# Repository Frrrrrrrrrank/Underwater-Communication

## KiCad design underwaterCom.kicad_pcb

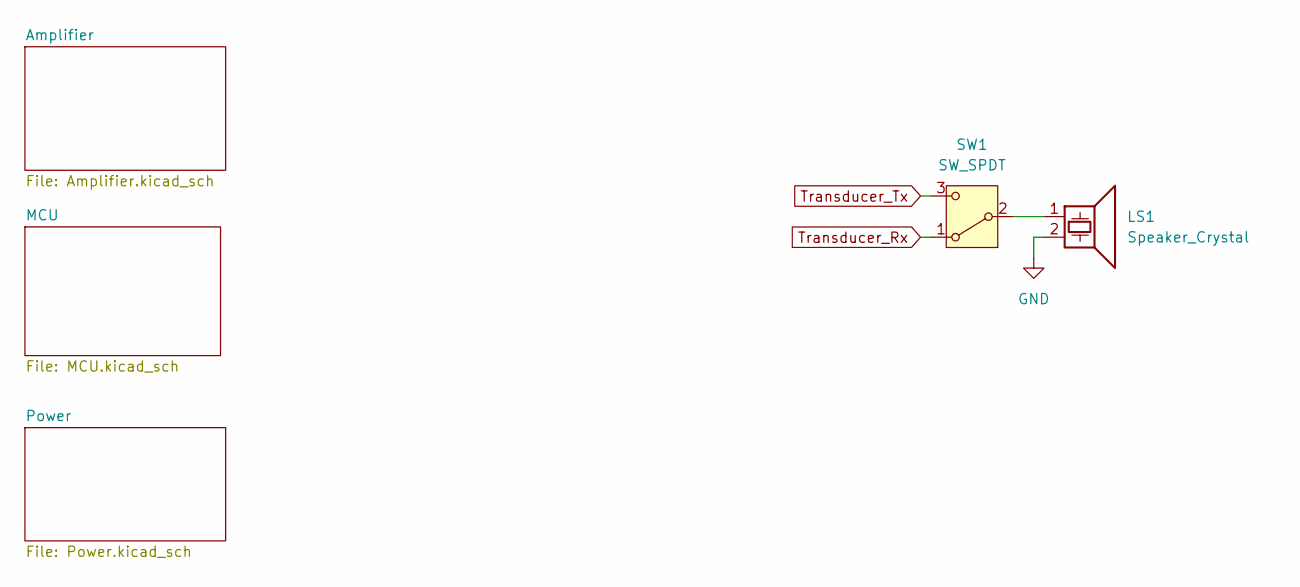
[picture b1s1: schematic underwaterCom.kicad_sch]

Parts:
LS1: Speaker_Crystal; PinHeader_1x02_P2.54mm_Vertical
SW1: SW_SPDT; Nidec_Copal_CAS-120A

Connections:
GND: LS1.2; also elsewhere on the board
unnamed: LS1.1, SW1.2 (B)
Transducer_Rx: SW1.1 (A); also elsewhere on the board
Transducer_Tx: SW1.3 (C); also elsewhere on the board

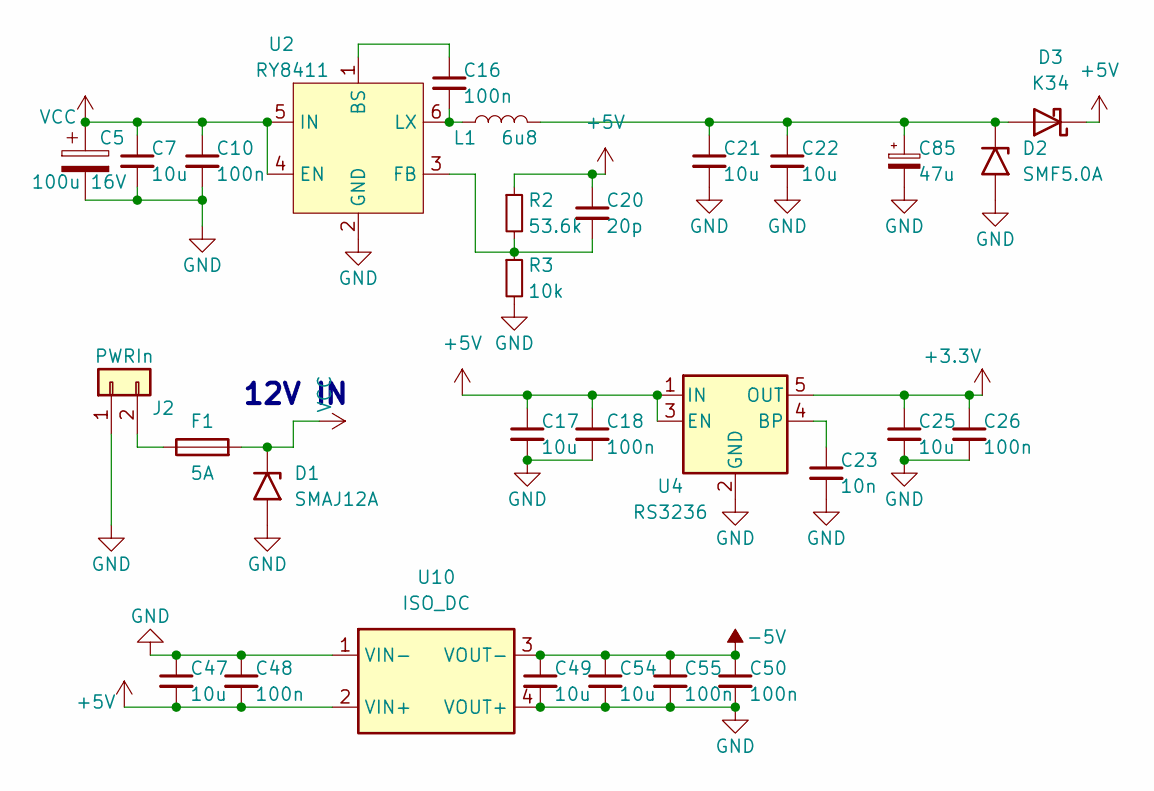
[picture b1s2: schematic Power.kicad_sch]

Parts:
C5: 100u 16V; CP_Radial_D6.3mm_P2.50mm
C7, C21, C22: 10u; C_1206_3216Metric
C10, C16, C18, C26, C48, C50, C55: 100n; C_0603_1608Metric
C17, C25, C47, C49, C54: 10u; C_0603_1608Metric
C20: 20p; C_0603_1608Metric
C23: 10n; C_0603_1608Metric
C85: 47u; CP_EIA-3216-18_Kemet-A_Pad1.58x1.35mm_HandSolder
D1: SMAJ12A; D_SMA
D2: SMF5.0A; D_SMF
D3: K34; D_SOD-123F
F1: 5A; Fuse_1206_3216Metric
J2: PWRIn; AMASS_XT30U-M_1x02_P5.0mm_Vertical
L1: 6u8; L_Sunlord_MWSA0402S
R2: 53.6k; R_0603_1608Metric
R3: 10k; R_0603_1608Metric
U2: RY8411; SOT-23-6
U4: RS3236; SOT-23-5
U10: ISO_DC; ISO_POWER

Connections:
+3.3V: C25.1, C26.1, U4.5 (OUT); also elsewhere on the board
+5V: C17.1, C18.1, C20.1, C47.2, C48.2, D3.1 (K), R2.1, U4.1 (IN), U4.3 (EN), U10.2 (VIN+); also elsewhere on the board
-5V: C49.1, C50.1, C54.1, C55.1, U10.3 (VOUT-); also elsewhere on the board
GND: C5.2, C7.2, C10.2, C17.2, C18.2, C21.2, C22.2, C23.2, C25.2, C26.2, C47.1, C48.1, C49.2, C50.2, C54.2, C55.2, C85.2, D1.2 (A2), D2.2 (A2), J2.1, R3.2, U2.2 (GND), U4.2 (GND), U10.1 (VIN-), U10.4 (VOUT+); also elsewhere on the board
unnamed: C21.1, C22.1, C85.1, D2.1 (A1), D3.2 (A), L1.2
unnamed: F1.1, J2.2
unnamed: C16.1, U2.1 (BS)
unnamed: C20.2, R2.2, R3.1, U2.3 (FB)
unnamed: C16.2, L1.1, U2.6 (LX)
unnamed: C23.1, U4.4 (BP)
VCC: C5.1, C7.1, C10.1, D1.1 (A1), F1.2, U2.4 (EN), U2.5 (IN); also elsewhere on the board

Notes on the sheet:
12V IN

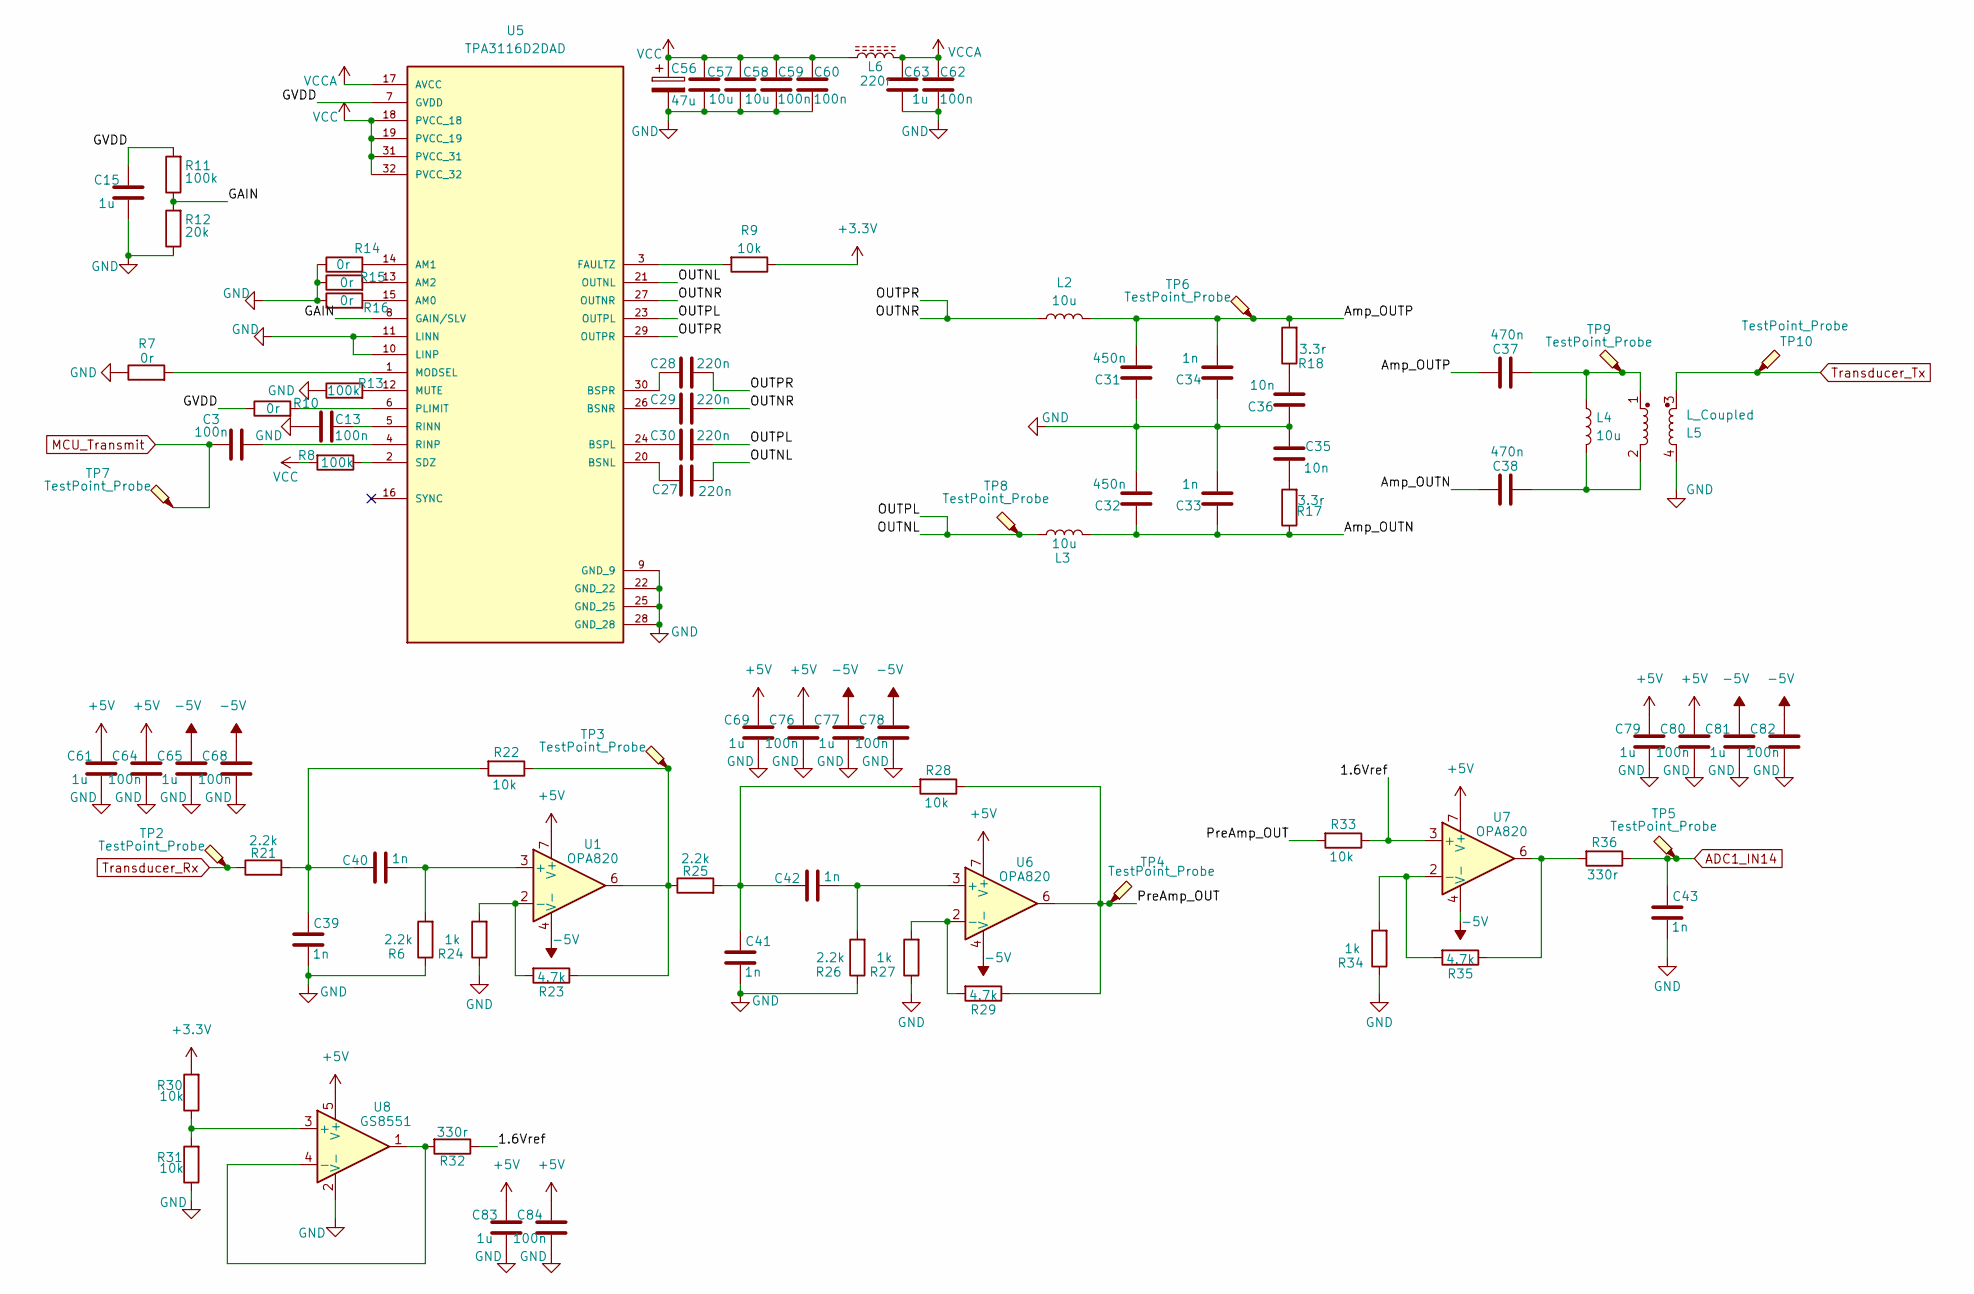
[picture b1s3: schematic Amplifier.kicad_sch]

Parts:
C3, C13, C59, C60, C62, C64, C68, C76, C78, C80, C82, C84: 100n; C_0603_1608Metric
C15, C61, C63, C65, C69, C77, C79, C81, C83: 1u; C_0603_1608Metric
C27, C28, C29, C30: 220n; C_0603_1608Metric
C31, C32: 450n; C_0603_1608Metric
C33, C34, C39, C40, C41, C42, C43: 1n; C_0603_1608Metric
C35, C36: 10n; C_0603_1608Metric
C37, C38: 470n; C_1206_3216Metric
C56: 47u; CP_Radial_D6.3mm_P2.50mm
C57, C58: 10u; C_1206_3216Metric
L2, L3, L4: 10u; L_Sunlord_MWSA0402S
L5: L_Coupled; L_CommonModeChoke_TDK_ATB322515
L6: 220r; L_0603_1608Metric
R6, R21, R25, R26: 2.2k; R_0603_1608Metric
R7, R10, R14, R15, R16: 0r; R_0603_1608Metric
R8, R11, R13: 100k; R_0603_1608Metric
R9, R22, R28, R30, R31, R33: 10k; R_0603_1608Metric
R12: 20k; R_0603_1608Metric
R17, R18: 3.3r; R_0603_1608Metric
R23, R29, R35: 4.7k; R_0603_1608Metric
R24, R27, R34: 1k; R_0603_1608Metric
R32, R36: 330r; R_0603_1608Metric
TP2, TP3, TP4, TP5, TP6, TP7, TP8, TP9, TP10: TestPoint_Probe; Testpoint_1.2_0.8
U1, U6, U7: OPA820; SOIC-8_3.9x4.9mm_P1.27mm
U5: TPA3116D2DAD; SOP65P810X115-32N; PARTREV G
U8: GS8551; SOT-23-5

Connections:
+3.3V: R9.1, R30.2; also elsewhere on the board
+5V: C61.2, C64.2, C69.2, C76.2, C79.2, C80.2, C83.2, C84.2, U1.7 (V+), U6.7 (V+), U7.7 (V+), U8.5 (V+); also elsewhere on the board
-5V: C65.2, C68.2, C77.2, C78.2, C81.2, C82.2, U1.4 (V-), U6.4 (V-), U7.4 (V-); also elsewhere on the board
/Amplifier/1.6Vref: R32.1, R33.1, U7.3 (+)
/Amplifier/Amp_OUTN: C32.2, C33.2, C38.1, L3.2, R17.1
/Amplifier/Amp_OUTP: C31.1, C34.1, C37.1, L2.2, R18.2, TP6.1
/Amplifier/GAIN: R11.1, R12.2, U5.8 (GAIN/SLV)
/Amplifier/GVDD: C15.2, R10.1, R11.2, U5.7 (GVDD)
/Amplifier/OUTNL: C27.1, C30.1, L3.1, TP8.1, U5.21 (OUTNL), U5.23 (OUTPL)
/Amplifier/OUTNR: C28.1, C29.1, L2.1, U5.27 (OUTNR), U5.29 (OUTPR)
/Amplifier/PreAmp_OUT: R28.1, R29.1, R33.2, TP4.1, U6.6
ADC1_IN14: C43.2, R36.1, TP5.1; also elsewhere on the board
GND: C13.1, C15.1, C31.2, C32.1, C33.1, C34.2, C35.2, C36.2, C39.1, C41.1, C43.1, C56.2, C57.2, C58.2, C59.1, C60.1, C61.1, C62.1, C63.1, C64.1, C65.1, C68.1, C69.1, C76.1, C77.1, C78.1, C79.1, C80.1, C81.1, C82.1, C83.1, C84.1, L5.4, R6.1, R7.1, R12.1, R13.1, R14.1, R15.1, R16.1, R24.1, R26.1, R27.1, R31.1, R34.1, U5.9 (GND_9), U5.10 (LINP), U5.11 (LINN), U5.22 (GND_22), U5.25 (GND_25), U5.28 (GND_28), U8.2 (V-); also elsewhere on the board
MCU_Transmit: C3.1, TP7.1; also elsewhere on the board
unnamed: C35.1, R17.2
unnamed: C36.1, R18.1
unnamed: C37.2, L4.1, L5.1, TP9.1
unnamed: C38.2, L4.2, L5.2
unnamed: C39.2, C40.2, R21.2, R22.2
unnamed: C41.2, C42.2, R25.2, R28.2
unnamed: R22.1, R23.1, R25.1, TP3.1, U1.6
unnamed: R35.1, R36.2, U7.6
unnamed: C40.1, R6.2, U1.3 (+)
unnamed: R23.2, R24.2, U1.2 (-)
unnamed: R16.2, U5.15 (AM0)
unnamed: R14.2, U5.14 (AM1)
unnamed: R15.2, U5.13 (AM2)
unnamed: C27.2, U5.20 (BSNL)
unnamed: C29.2, U5.26 (BSNR)
unnamed: C30.2, U5.24 (BSPL)
unnamed: C28.2, U5.30 (BSPR)
unnamed: R9.2, U5.3 (FAULTZ)
unnamed: R7.2, U5.1 (MODSEL)
unnamed: R13.2, U5.12 (MUTE)
unnamed: R10.2, U5.6 (PLIMIT)
unnamed: C13.2, U5.5 (RINN)
unnamed: C3.2, U5.4 (RINP)
unnamed: R8.1, U5.2 (SDZ)
unnamed: C42.1, R26.2, U6.3 (+)
unnamed: R27.2, R29.2, U6.2 (-)
unnamed: R34.2, R35.2, U7.2 (-)
unnamed: R30.1, R31.2, U8.3 (+)
unnamed: R32.2, U8.1, U8.4 (-)
Transducer_Rx: R21.1, TP2.1; also elsewhere on the board
Transducer_Tx: L5.3, TP10.1; also elsewhere on the board
VCC: C56.1, C57.1, C58.1, C59.2, C60.2, L6.1, R8.2, U5.18 (PVCC_18), U5.19 (PVCC_19), U5.31 (PVCC_31), U5.32 (PVCC_32); also elsewhere on the board
VCCA: C62.2, C63.2, L6.2, U5.17 (AVCC)

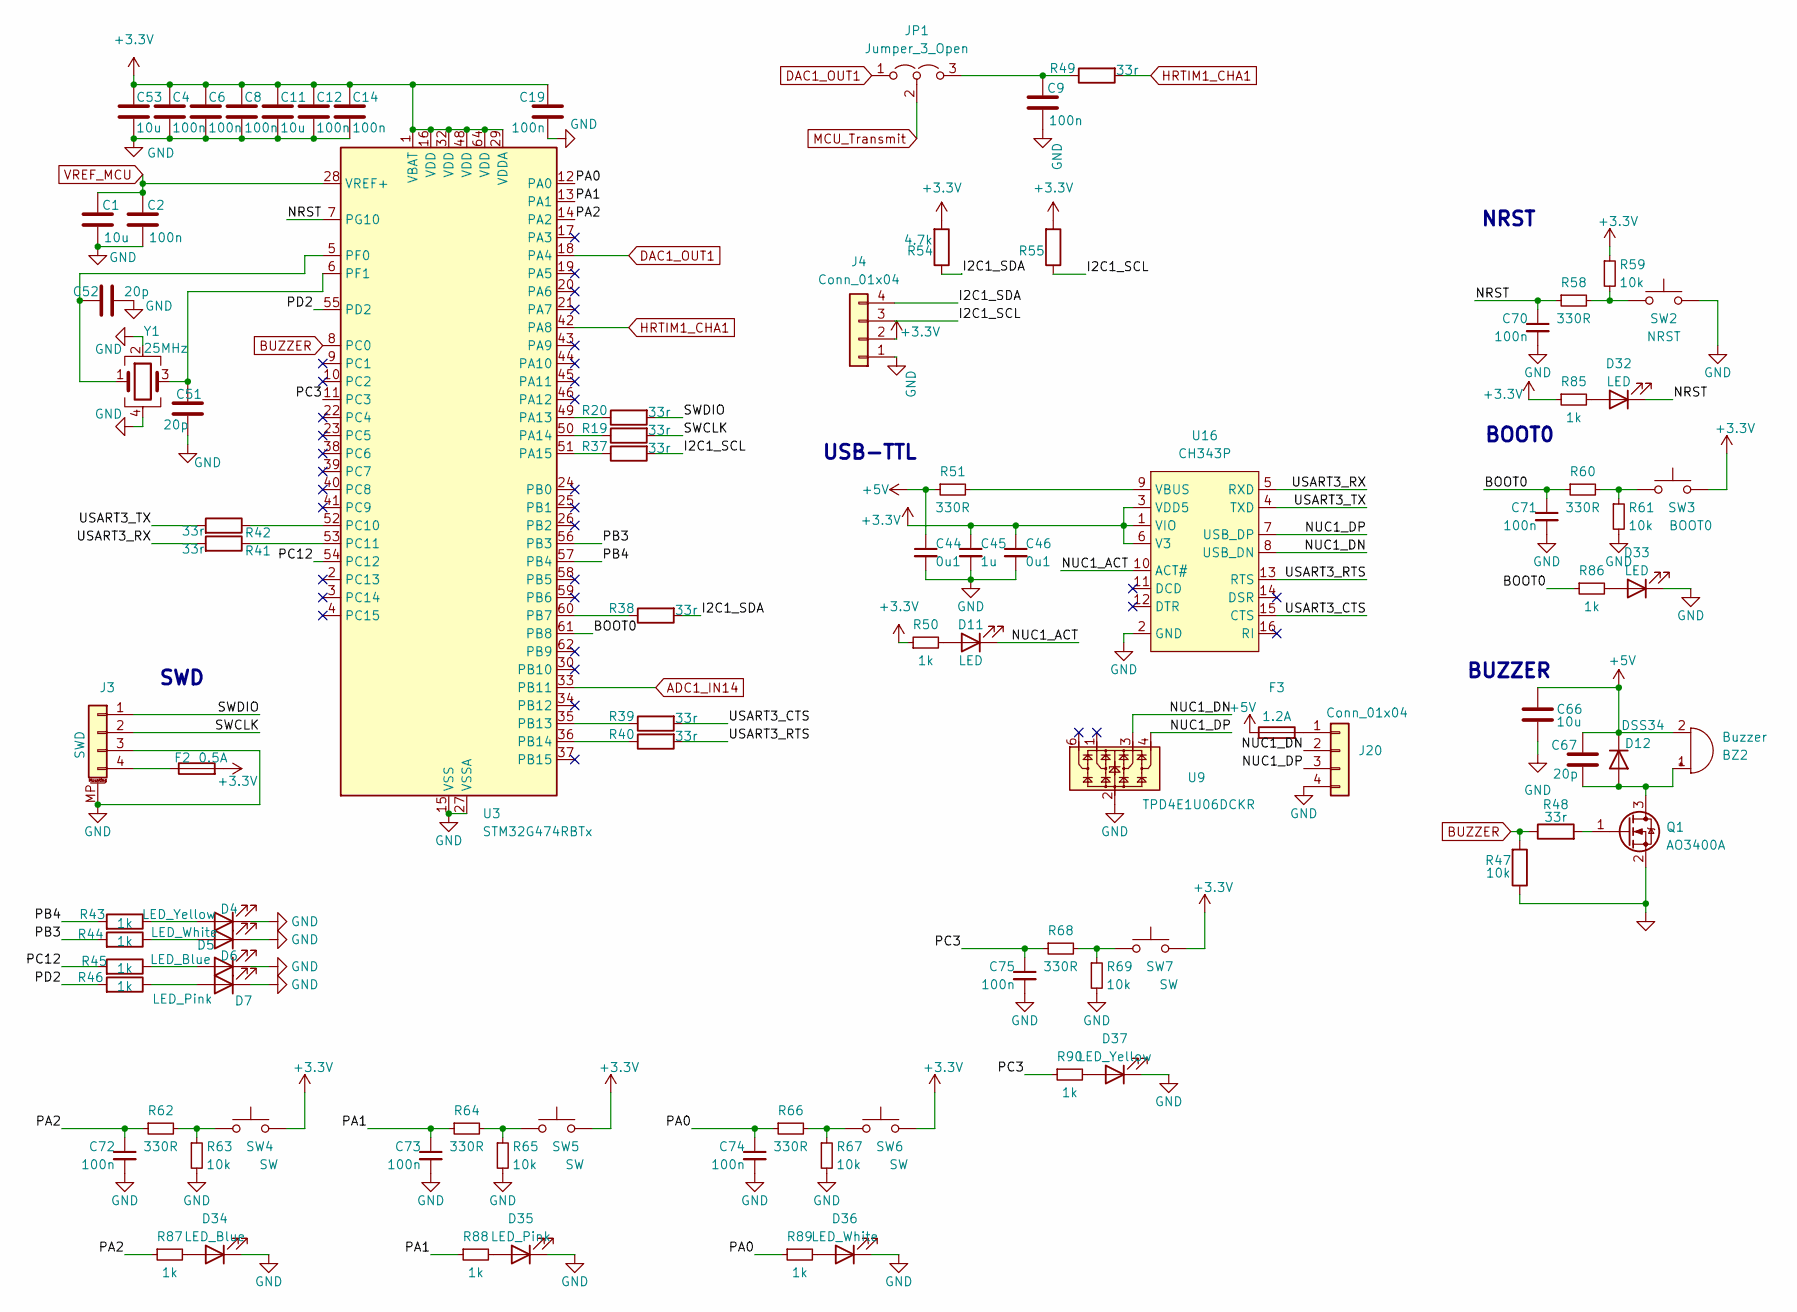
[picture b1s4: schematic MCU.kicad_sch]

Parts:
BZ2: Buzzer; MLT-9032
C1, C11, C53, C66: 10u; C_0603_1608Metric
C2, C4, C6, C8, C9, C12, C14, C19, C70, C71, C72, C73, C74, C75: 100n; C_0603_1608Metric
C44, C46: 0u1; C_0603_1608Metric
C45: 1u; C_0603_1608Metric
C51, C52, C67: 20p; C_0603_1608Metric
D4, D37: LED_Yellow; LED_0603_1608Metric
D5, D36: LED_White; LED_0603_1608Metric
D6, D34: LED_Blue; LED_0603_1608Metric
D7, D35: LED_Pink; LED_0603_1608Metric
D11, D32, D33: LED; LED_0603_1608Metric
D12: DSS34; D_SMF
F2: 0.5A; Fuse_1206_3216Metric
F3: 1.2A; Fuse_1210_3225Metric
J3: SWD; Molex_PicoBlade_53261-0471_1x04-1MP_P1.25mm_Horizontal
J4: Conn_01x04; PinHeader_1x04_P2.54mm_Vertical
J20: Conn_01x04; JST_PH_B4B-PH-K_1x04_P2.00mm_Vertical
JP1: Jumper_3_Open; PinHeader_1x03_P1.00mm_Vertical
Q1: AO3400A; SOT-23
R19, R20, R37, R38, R39, R40, R41, R42, R48, R49: 33r; R_0603_1608Metric
R43, R44, R45, R46, R50, R85, R86, R87, R88, R89, R90: 1k; R_0603_1608Metric
R47, R59, R61, R63, R65, R67, R69: 10k; R_0603_1608Metric
R51, R58, R60, R62, R64, R66, R68: 330R; R_0603_1608Metric
R54, R55: 4.7k; R_0603_1608Metric
SW2: NRST; Panasonic_EVQPUL_EVQPUC
SW3: BOOT0; Panasonic_EVQPUL_EVQPUC
SW4, SW5, SW6, SW7: SW; SW_SPST_TL3342
U3: STM32G474RBTx; LQFP-64_10x10mm_P0.5mm
U9: TPD4E1U06DCKR; SOT-363_SC-70-6
U16: CH343P; TQFN-16-1EP_3x3mm_P0.5mm_EP1.6x1.6mm
Y1: 25MHz; Crystal_SMD_3225-4Pin_3.2x2.5mm

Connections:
+3.3V: C4.1, C6.1, C8.1, C11.1, C12.1, C14.1, C19.1, C45.1, C46.1, C53.1, F2.2, J4.2, R50.1, R54.2, R55.2, R59.1, R85.1, SW3.2, SW4.2, SW5.2, SW6.2, SW7.2, U3.1 (VBAT), U3.16 (VDD), U3.29 (VDDA), U3.32 (VDD), U3.48 (VDD), U3.64 (VDD), U16.1 (VIO), U16.3 (VDD5), U16.6 (V3); also elsewhere on the board
+5V: BZ2.2 (-), C44.1, C66.1, C67.1, D12.1 (K), F3.1, R51.1; also elsewhere on the board
/MCU/BOOT0: C71.1, R60.1, R86.1, U3.61 (PB8)
/MCU/I2C1_SCL: J4.3, R37.2, R55.1
/MCU/I2C1_SDA: J4.4, R38.2, R54.1
/MCU/NRST: C70.1, D32.1 (K), R58.1, U3.7 (PG10)
/MCU/NUC1_ACT: D11.1 (K), U16.10 (ACT#)
/MCU/NUC1_DN: J20.2, U9.3, U16.8 (USB_DN)
/MCU/NUC1_DP: J20.3, U9.4, U16.7 (USB_DP)
/MCU/PA0: C74.1, R66.1, R89.1, U3.12 (PA0)
/MCU/PA1: C73.1, R64.1, R88.1, U3.13 (PA1)
/MCU/PA2: C72.1, R62.1, R87.1, U3.14 (PA2)
/MCU/PB3: R44.2, U3.56 (PB3)
/MCU/PB4: R43.2, U3.57 (PB4)
/MCU/PC3: C75.1, R68.1, R90.1, U3.11 (PC3)
/MCU/PC12: R45.2, U3.54 (PC12)
/MCU/PD2: R46.2, U3.55 (PD2)
/MCU/SWCLK: J3.2, R19.2
/MCU/SWDIO: J3.1, R20.2
/MCU/USART3_CTS: R39.2, U16.15 (CTS)
/MCU/USART3_RTS: R40.2, U16.13 (RTS)
/MCU/USART3_RX: R41.2, U16.5 (RXD)
/MCU/USART3_TX: R42.2, U16.4 (TXD)
ADC1_IN14: U3.33 (PB11); also elsewhere on the board
BUZZER: R47.2, R48.1, U3.8 (PC0)
DAC1_OUT1: JP1.1 (A), U3.18 (PA4)
GND: C1.2, C2.2, C4.2, C6.2, C8.2, C9.2, C11.2, C12.2, C14.2, C19.2, C44.2, C45.2, C46.2, C51.2, C52.2, C53.2, C66.2, C70.2, C71.2, C72.2, C73.2, C74.2, C75.2, D4.1 (K), D5.1 (K), D6.1 (K), D7.1 (K), D33.1 (K), D34.1 (K), D35.1 (K), D36.1 (K), D37.1 (K), J3.3, J3.MP (MountPin), J4.1, J20.4, Q1.2 (S), R47.1, R61.2, R63.2, R65.2, R67.2, R69.2, SW2.2, U3.15 (VSS), U3.27 (VSSA), U3.31 (VSS), U3.47 (VSS), U3.63 (VSS), U9.2, U16.2 (GND), U16.17 (GND), Y1.2, Y1.4; also elsewhere on the board
HRTIM1_CHA1: R49.2, U3.42 (PA8)
MCU_Transmit: JP1.2 (C); also elsewhere on the board
unnamed: BZ2.1 (+), C67.2, D12.2 (A), Q1.3 (D)
unnamed: D4.2 (A), R43.1
unnamed: D5.2 (A), R44.1
unnamed: D6.2 (A), R45.1
unnamed: D7.2 (A), R46.1
unnamed: D11.2 (A), R50.2
unnamed: D32.2 (A), R85.2
unnamed: D33.2 (A), R86.2
unnamed: D34.2 (A), R87.2
unnamed: D35.2 (A), R88.2
unnamed: D36.2 (A), R89.2
unnamed: D37.2 (A), R90.2
unnamed: F2.1, J3.4
unnamed: F3.2, J20.1
unnamed: C9.1, JP1.3 (B), R49.1
unnamed: Q1.1 (G), R48.2
unnamed: R58.2, R59.2, SW2.1
unnamed: R60.2, R61.1, SW3.1
unnamed: R62.2, R63.1, SW4.1
unnamed: R64.2, R65.1, SW5.1
unnamed: R66.2, R67.1, SW6.1
unnamed: R68.2, R69.1, SW7.1
unnamed: R20.1, U3.49 (PA13)
unnamed: R19.1, U3.50 (PA14)
unnamed: R37.1, U3.51 (PA15)
unnamed: R38.1, U3.60 (PB7)
unnamed: R39.1, U3.35 (PB13)
unnamed: R40.1, U3.36 (PB14)
unnamed: R42.1, U3.52 (PC10)
unnamed: R41.1, U3.53 (PC11)
unnamed: C52.1, U3.5 (PF0), Y1.1
unnamed: C51.1, U3.6 (PF1), Y1.3
unnamed: R51.2, U16.9 (VBUS)
VREF_MCU: C1.1, C2.1, U3.28 (VREF+)

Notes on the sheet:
SWD
BUZZER
BOOT0
USB-TTL
NRST

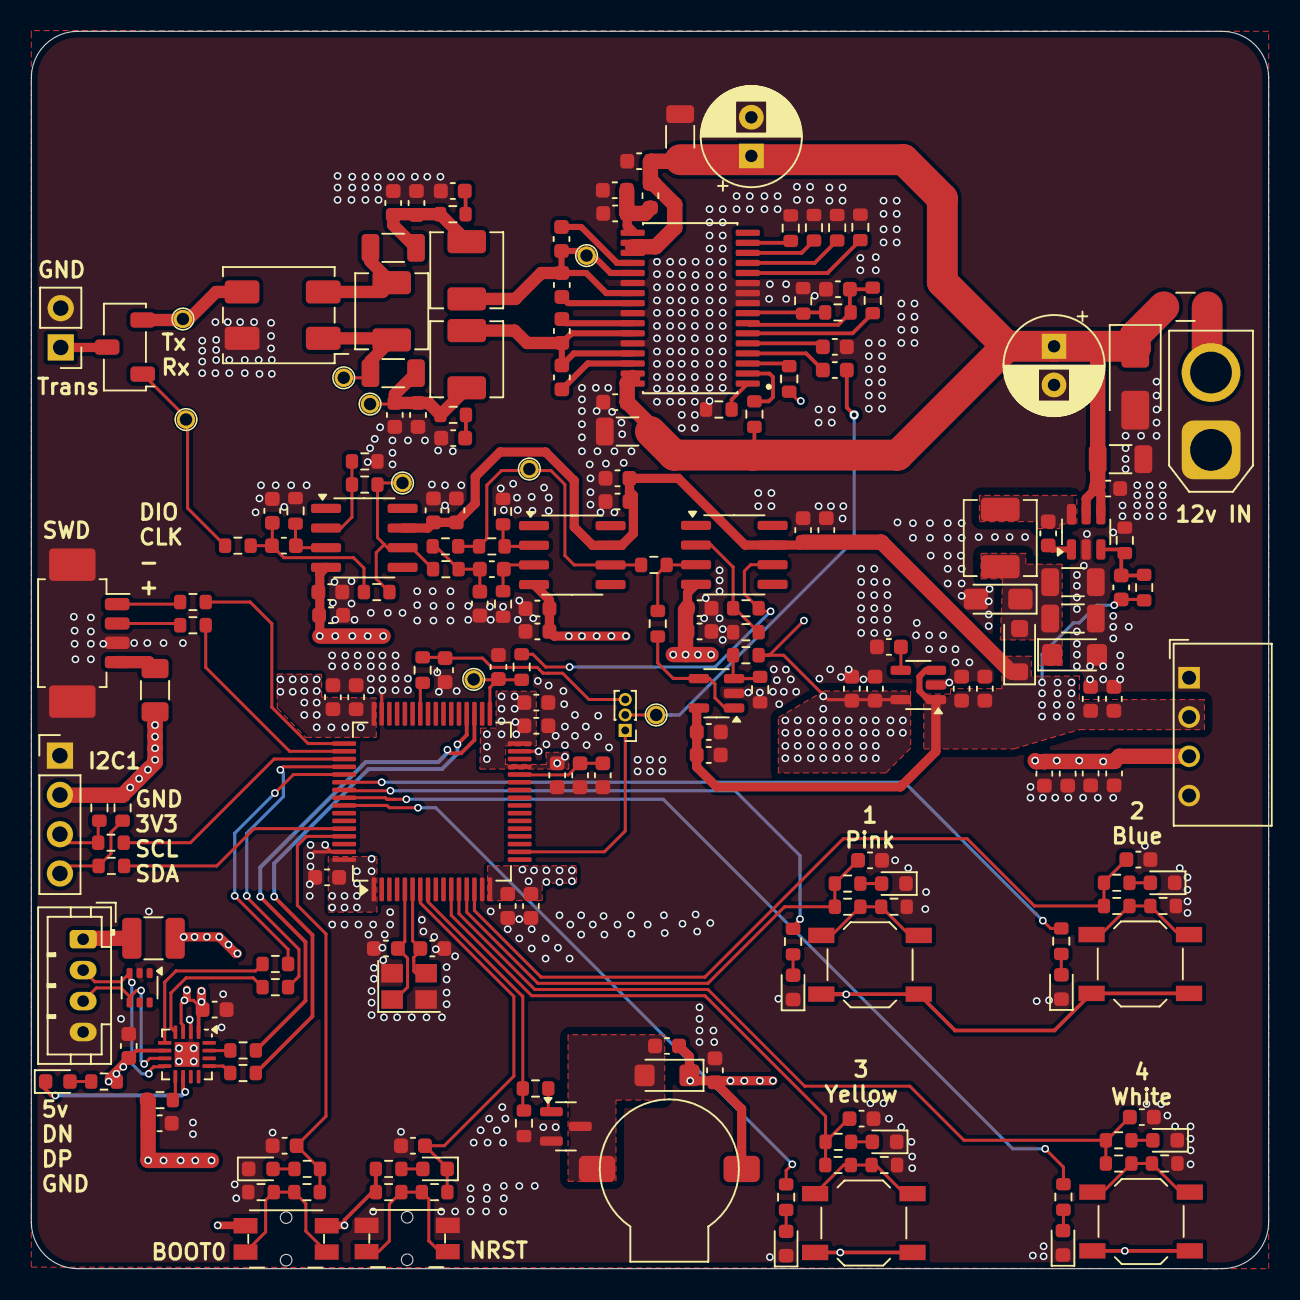
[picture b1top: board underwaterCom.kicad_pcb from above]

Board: 4 copper layers, 80.0 x 80.0 mm, 212 parts (0 on the bottom side), 112 nets.

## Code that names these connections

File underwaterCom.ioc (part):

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Mcu.Name=STM32G474R(B-C-E)Tx
Mcu.Package=LQFP64
Mcu.UserName=STM32G474RBTx
PA0.Signal=GPIO_Input
PA1.Signal=GPIO_Input
PA13.Mode=Serial_Wire
PA13.Signal=SYS_JTMS-SWDIO
PA14.Mode=Serial_Wire
PA14.Signal=SYS_JTCK-SWCLK
PA15.Mode=I2C
PA15.Signal=I2C1_SCL
PA2.Signal=GPIO_Input
PA4.Signal=COMP_DAC11_group
PA8.Mode=Output_TA1
PA8.Signal=HRTIM1_CHA1
PB11.Mode=IN14-Single-Ended
PB11.Signal=ADC1_IN14
PB13.Mode=CTS_RTS
PB13.Signal=USART3_CTS
PB14.Mode=CTS_RTS
PB14.Signal=USART3_RTS
PB3.Signal=GPIO_Output
PB4.Signal=GPIO_Output
PB7.Mode=I2C
PB7.Signal=I2C1_SDA
PC0.Signal=S_TIM1_CH1
PC10.Mode=Asynchronous
PC10.Signal=USART3_TX
PC11.Mode=Asynchronous
PC11.Signal=USART3_RX
PC12.Signal=GPIO_Output
PC3.Signal=GPIO_Input
PD2.Signal=GPIO_Output
PF0-OSC_IN.Mode=HSE-External-Oscillator
PF0-OSC_IN.Signal=RCC_OSC_IN
PF1-OSC_OUT.Mode=HSE-External-Oscillator
PF1-OSC_OUT.Signal=RCC_OSC_OUT
RCC.HSE_VALUE=25000000
RCC.SYSCLKFreq_VALUE=170000000
RCC.SYSCLKSource=RCC_SYSCLKSOURCE_PLLCLK
board=custom

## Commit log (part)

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2026-06-12 layout finish,send manufature
